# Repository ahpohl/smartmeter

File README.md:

# Overview

The project started when my mechanical [Ferraris energy counter](https://en.wikipedia.org/wiki/Electricity_meter) was replaced with a digital [smart meter](resources/ebz/datenblatt_dd3.pdf) from eBZ. The DD3 model provides an IR signal which can be read once a second with a simple IR receiver. Initially I used just an Arduino with a [photo transistor circuit](https://github.com/ahpohl/smartmeter/wiki/Arduino-breadboard) on a breadboard to read the signal. Later I have built an [IR dongle](https://github.com/ahpohl/smartmeter/wiki/IR-dongle-pcb) on a real PCB in a nice case for permanent mounting on top of the smart meter.

For the software side, the Smartmeter program reads the raw stream of data from the energy meter and forwards it as a JSON formatted string to a MQTT broker on the network. The data is stored in a TimescaleDB database and visualised on a Grafana dashboard. The installation of the software stack including the setup and maintainance of the database is described on separate [wiki pages](https://github.com/ahpohl/smartmeter/wiki).

## Build instructions

If you need to compile Smartmeter directly from source, a Makefile for (cross-)compilation is provided:

```
make CROSS_COMPILE=aarch64-unknown-linux-gnu
make install
```

Alternatively, there is also an Arch Linux package of [Smartmeter](https://aur.archlinux.org/packages/smartmeter) published in the AUR. 

## Installation

The Arch Linux package provides a systemd service file and installs the configuration file in `/etc/smartmeter/smartmeter.conf`. The service can be started with:

```
systemctl start smartmeter
```

When building directly from source, the daemon can be directly started with:

```
smartmeter --config resources/config/smartmeter_example.conf

```

## Run in Docker

The Arch Linux package installs a docker compose in `/etc/smartmeter/docker-compose.yaml` and a `Dockerfile`. Alternatively, these files are also in the root folder or the source. Before building and starting the container, the serial device used by the IR dongle needs to be set in `docker-compose.yaml` in addtion to `smartmeter.conf` to give Docker access to the IR dongle device.

```
docker-compose up --build
```

## Configuration

The Smartmeter program is configured with a configuration file located in `/etc/smartmeter/smartmeter.conf`. At least the serial device of the IR dongle, the MQTT hostname and topic to publish to needs to be set. Optionally, Smartmeter supports MQTT password authentication and TLS connection encryption. Finally, the electricity tariff, which usually consistsa price per kWh and a monthly (yearly) charge, needs to be set here for the current bill to be shown on the dashboard.

A minimal `smartmeter.conf` config file looks like this:

```
serial_device /dev/ttyUSB0
mqtt_topic smartmeter
mqtt_broker localhost
basic_rate 175.91
price_kwh 0.1983
```

## Smartmeter output

There are two versions of the EBz smart meter, the OD-types and the SM-types. According to the [manual](resources/ebz/ebz_manual.pdf), the OD-type uses the following communication parameters: 9600 Baud, 7 data bits, even parity and 1 stop bit. The serial data can be read directly with a terminal program such as picocom:

```
picocom -b 9600 -d 7 -y e /dev/ttyUSB0

/EBZ5DD3BZ06ETA_107                # '/' start marker, serial number

1-0:0.0.0*255(1EBZ0100507409)      # custom ID
1-0:96.1.0*255(1EBZ0100507409)     # device ID
1-0:1.8.0*255(000125.25688570*kWh) # energy meter
1-0:16.7.0*255(000259.20*W)        # total power
1-0:36.7.0*255(000075.18*W)        # L1 phase power
1-0:56.7.0*255(000092.34*W)        # L2 phase power
1-0:76.7.0*255(000091.68*W)        # L3 phase power
1-0:32.7.0*255(232.4*V)            # L1 phase voltage
1-0:52.7.0*255(231.7*V)            # L2 phase voltage
1-0:72.7.0*255(233.7*V)            # L3 phase voltage
1-0:96.5.0*255(001C0104)           # status
0-0:96.8.0*255(00104443)           # sensor lifetime in secs, 0x
!                                  # '!' end marker
```

Example JSON published by Smartmeter in the `smartmeter/live` topic:

```
[{
  "lifetime":150705410,     # sensor lifetime in secs, 0x
  "energy":17894.01494491,  # AC energy, kWh
  "power":228.46,           # AC power, W
  "power_l1":47.5,          # AC L1 phase power, W 
  "power_l2":66.68,         # AC L2 phase power, W
  "power_l3":114.28,        # AC L3 phase power, W
  "voltage_l1":233.1,       # Voltage L1 phase, V
  "voltage_l2":231.4,       # Voltage L2 phase, V
  "voltage_l3":233,         # Voltage L3 phase, V
  "status":"001C0104",      # EBz status
  "rate":246.13,            # price plan serice charge, € (or whatever)
  "price":0.2445,           # cost per kWh
  "time":1729973193908      # timestamp, secs since epoch
},
{
  "serial":"EBZ5DD3BZ06ETA_107",
  "custom_id":"1EBZ0100507409",
  "device_id":"1EBZ0100507409"
}]
```

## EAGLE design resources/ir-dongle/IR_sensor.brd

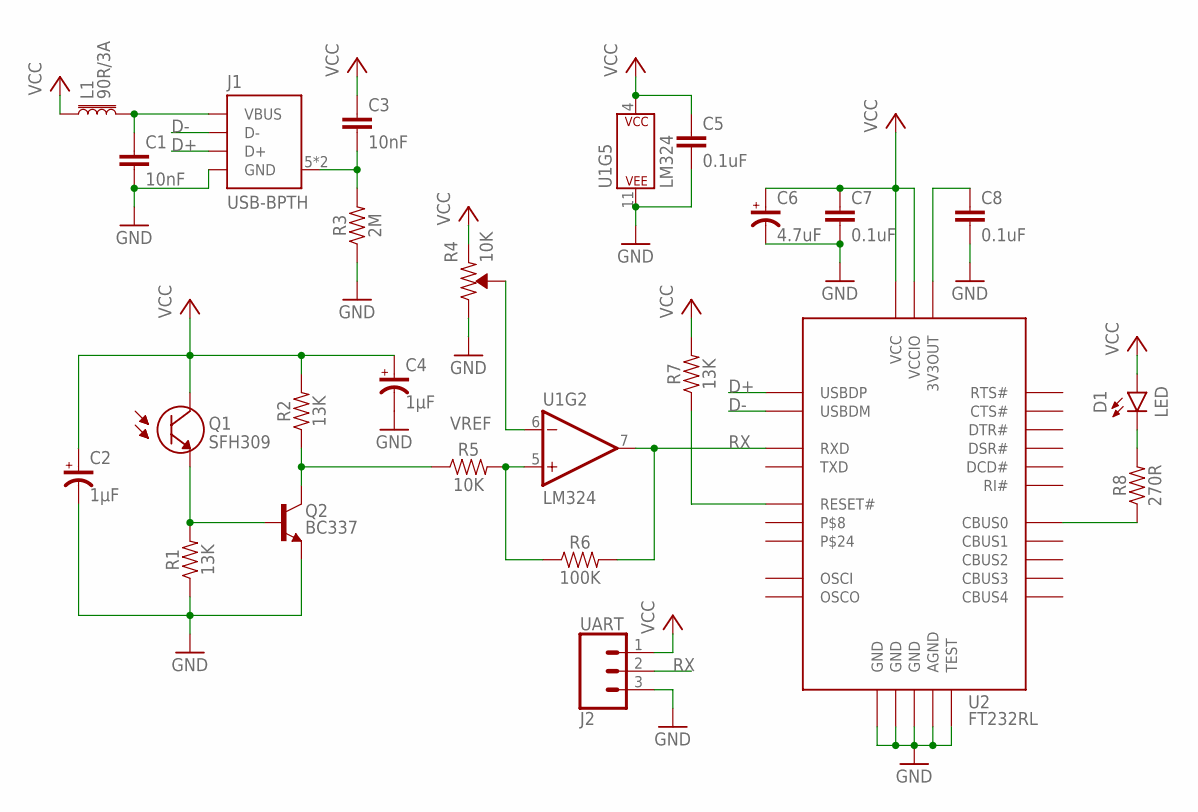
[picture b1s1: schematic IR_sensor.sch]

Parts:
C1: 10nF; CAP-PTH-2.5MM
C2, C4: 1µF; CPOL-RADIAL-2.5MM-5MM
C3: 10nF; CAP-PTH-5MM
C5, C7, C8: 0.1uF; CAP-PTH-5MM
C6: 4.7uF; CPOL-RADIAL-2.5MM-5MM
D1: LED; LED_5MM
J1: USB-BPTH; USB-B-PTH
J2: UART; 1X03
L1: 90R/3A; AXIAL-0.3
Q1: SFH309; LED_3MM_R
Q2: BC337; TO-92
R1, R2, R7: 13K; AXIAL-0.3
R3: 2M; AXIAL-0.3
R4: 10K; TRIMPOT
R5: 10K; AXIAL-0.3
R6: 100K; AXIAL-0.3
R8: 270R; AXIAL-0.3
U1: LM324; DIP14
U2: FT232RL; TSSOP-28-BL

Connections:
ADC: Q2.3 (C), R2.P$1 (1), R5.P$1 (1)
D+: J1.3 (D+), U2.15 (USBDP)
D-: J1.2 (D-), U2.16 (USBDM)
GND: C1.2, C2.2 (-), C4.2 (-), C5.2, C6.2 (-), C7.2, C8.2, J1.4 (GND), J2.3, Q2.1 (E), R1.P$1 (1), R3.P$1 (1), R4.P$2 (CW), U1.11 (P$V-), U2.7 (GND), U2.18 (GND), U2.21 (GND), U2.25 (AGND), U2.26 (TEST)
unnamed: C1.1, J1.1 (VBUS), L1.P$2 (2)
unnamed: R5.P$2 (2), R6.P$1 (1), U1.5 (+IN)
unnamed: Q1.A (E), Q2.2 (B), R1.P$2 (2)
unnamed: C8.1, U2.17 (3V3OUT)
unnamed: D1.K, R8.P$2 (2)
unnamed: R8.P$1 (1), U2.23 (CBUS0)
unnamed: C3.2, J1.5 (SHIELD), J1.6 (SHIELD), R3.P$2 (2)
unnamed: R7.P$1 (1), U2.19 (RESET#)
RX: J2.2, R6.P$2 (2), U1.7 (OUT), U2.5 (RXD)
VCC: C2.1 (+), C3.1, C4.1 (+), C5.1, C6.1 (+), C7.1, D1.A, J2.1, L1.P$1 (1), Q1.K (C), R2.P$2 (2), R4.P$1 (CCW), R7.P$2 (2), U1.4 (P$V+), U2.4 (VCCIO), U2.20 (VCC)
VREF: R4.P$3 (WIPER), U1.6 (-IN)

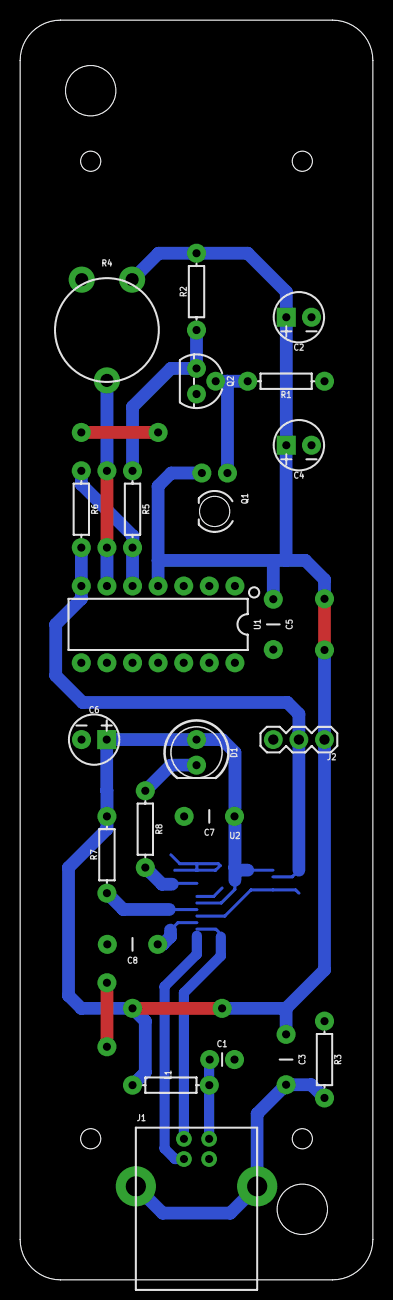
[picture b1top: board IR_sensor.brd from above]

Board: 2 copper layers, 35.0 x 125.0 mm, 24 parts (0 on the bottom side), 15 nets.

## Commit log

2020-01-29 intital commit
2020-01-29 get d0 datagram from serial port
2020-01-29 added .gitignore
2020-01-29 make serial buffer static
2020-01-29 cleanup git build dir
2020-01-29 cleanup git main.o
2020-01-30 allocate dynamic serial buffer
2020-01-30 datagram validity check
2020-01-30 parsed serial num and device id
2020-01-30 read d0 datagram complete
2020-01-31 setup write obis thread
2020-01-31 smartmeter functional version
2020-01-31 fix wrong variable initialisation
2020-01-31 fix Makefile install target
2020-01-31 fix missing backslash
2020-01-31 convert sensor time to unsigned long
2020-01-31 fix sensor time format for meterN
2020-01-31 add sensor lifetime in days
2020-02-01 remove set ramdisk function
2020-02-01 const correctness
2020-08-12 publish to MQTT broker
2020-08-12 run MQTT publish in its own thread
2020-08-12 wait before publish obis and mqtt
2020-08-13 add topic parameter
2020-08-13 send MQTT every 10 minutes
2020-08-13 commented publish power to MQTT
2020-08-13 publish MQTT power only in debug
2020-08-14 initial README.md text
2020-08-14 add mqtt to influxdb bridge files
2020-08-14 remove MQTT power function
2020-08-15 remove unneeded includes
2020-08-15 publish MQTT json string
2020-08-15 convert m_sensortime to seconds only once
2020-08-15 control precsion of obex and mqtt output
2020-08-15 updated README influxdb
2020-08-15 set obis precision of lifetime
2020-08-15 MQTT json output fields and tags
2020-08-15 put lifetime output first
2020-08-15 MQTT json output as floats
2020-08-15 updated retention policy and continuous query
2020-08-15 README.md json fields and tags string
2020-08-15 remove mqtt to influxdb bridge script
2020-08-21 add node-red flow
2020-08-21 updated README, grafana dashboard
2020-08-22 add influxdb continuous queries into README
2020-08-23 modified grafana dashboard
2020-08-23 add electricity tariff details
2020-08-23 rename tariff options
2020-08-23 fix price and rate options
2020-08-24 add meterN dashboard
2020-08-24 mqtt rate and price move to fields
2020-08-29 fix path in smartmeter.conf
2020-09-04 add grafana dashboard screenshot
2020-09-20 updated README, inserted links
2020-12-04 mosq reconnect and resend
2020-12-04 publish in do while loop
2020-12-04 wait before reconnect
2020-12-04 add reconnect_async call
2021-01-05 basic rate per month
2021-01-05 add IR dongle schematics
2021-01-05 rename schematics
2021-01-05 correct schematic name
2021-01-05 add node-red flow chart
2021-01-05 updated grafana dash json
2021-02-15 updated schematic and dashboard
2021-03-08 include unix epoch timestamp with ms precision
2021-03-08 save timestamp earlier when receiving data
2021-03-08 timestamp before reading datagram
2021-03-09 timestamp protected by mutex
2021-03-13 singled threaded, keep obis codes
2021-03-13 handle shutdown with signals
2021-03-13 update changelog
2021-03-13 grafana flux queries
2021-03-13 rename flux query file
2021-03-13 update grafana flux queries
2021-03-13 add influxdb tasks
2021-03-13 daily task group results by field
2021-03-14 update daily task flux
2021-03-14 update daily task
2021-03-14 update and optimise daily task
2021-03-23 move status into json value array
2021-03-23 remove second time value
2021-03-23 move status up
2021-04-01 move from influxdb to timescaledb
2021-04-01 remove influxdb files
2021-04-02 clean up
2021-04-06 Delete IR-dongle_schematic.png
    MCP2221 does not support 7 bit data mode and hence does not work for the OD version of the smartmeter
2021-04-17 grafana dashboard timeseries plots
2021-04-17 add schematic with FT232RL
2021-04-19 add pcb process
2021-05-09 enable even parity checking
2021-05-09 add eagle files
2021-05-09 remove EOM from d0.log
2021-05-09 use shared pointer in main
2021-05-23 release publish online/offline status
2021-05-23 add auth to mqtt class
2021-05-23 support mqtt username and password
2021-05-23 fix type in config file
2021-05-23 change reason_code into connack_code
2021-05-25 enable TLS, no server cert checking, no client certs
2021-05-25 connection TLS enabled
2021-05-25 update readme and changelog
2021-05-26 Revert "Update README.md"
    This reverts commit c782abcb954976815a0ef9e2b79eb43e2e82a3e6.
2021-05-26 Revert "Update README.md"
    This reverts commit 4d74c51eb6688a3e69187eb757d56f544f73e49c.
2021-05-26 Revert "Update README.md"
    This reverts commit 95f2e60795c3afd906bca35778d2d0a31f4a2429.
2021-05-26 Revert "Update README.md"
    This reverts commit 7963ffcb9a89f0e7c2e197022705f80680d061c4.
2021-05-26 Revert "Update README.md"
    This reverts commit be89226843cce1d0f01fbb2af5f37c76624b0fd6.
2021-05-26 initial config parser
2021-05-26 config parser adapted
2021-05-26 rename variables
2021-05-26 read config file
2021-05-26 add config file with comments
2021-05-26 basic class setup complete
2021-05-26 convert string to type
2021-05-26 fill map with key value pairs
2021-05-26 ignore config executable
2021-05-26 parse key value pairs into map
2021-05-26 add display config function
2021-05-27 get value as inline function
2021-05-27 add const to methods
2021-05-27 make string default data type for GetValue
2021-05-27 implement get ... functions
2021-05-27 check valid_keys
2021-05-27 use config in smartmeter class
2021-05-27 edit main getopt arguments
2021-05-27 checking config arguments
2021-05-27 checked most arguments
2021-05-27 clean up includes, check config complete
2021-05-28 project cleanup
2021-05-28 enable TLS, add config file
2021-05-29 remove systemd config file
2021-05-30 updated sql scripts
2021-05-30 cagg average power
2021-05-30 updated grafana dashboard
2021-05-30 edit comments in sql scripts
2021-05-30 average power phases
2021-05-31 update grafana dashboard
2021-06-04 change cagg_power retention time
2021-06-13 publish data into /live topic
2021-06-16 rename pg_cron jobs
2021-09-26 add Dockerfile for node-red
2021-09-26 node-red credential file not working
2021-09-26 node-red credentials working
2021-09-27 docker node-red and timescaledb containers ok
2021-09-27 timescaledb container running
2021-09-28 move customizations to custom.sql
2021-10-03 Revert "add Dockerfile for node-red"
    This reverts commit c09ee220cf7a45331acffbf8682e2ff1631bd5a4.
2021-10-03 commit postgres wal archive scripts
2021-10-08 edit views.sql to include start date of archive
2022-01-02 set debug level in config file
2022-01-02 update node-red and grafana json
2022-01-07 node-red flow use smartmeter/live topic
2022-01-08 use timescaledb_experimental.time_bucket_ng()
2022-01-08 change pg_cron schedule
2022-02-02 remove indices on aggregate tables
2022-02-02 add unique constaint on archive bucket_1d
2022-02-02 insert comment in views.sql
2022-02-03 add unique indices for mat view refresh concurrently
2022-02-21 log buffer before sync check
2022-02-21 do not exit on serial receive error
2022-04-06 add averages to montly view
2022-10-30 update smartmeter.conf example
2022-12-29 update smartmeter mqtt class
2022-12-29 fix status online disappears after reconnect
2022-12-29 bump changelog to new version
2022-12-29 fix typo in online message
2022-12-29 add mqtt online notify flag
2023-02-14 updated retention policies
2023-04-12 remove experimental time_bucket
2023-04-15 time buckets at local time zone
2023-04-15 update monthly plot grafana dashboard
2023-07-22 plpgsql function to calc percentages
2023-08-18 add eclipse project and cross compile option
2023-08-18 remove log enum from serial and mqtt classes
2023-08-18 silence error messages after 5
2023-08-19 flush serial buffers after out of sync
2023-08-29 show sunrise and sunset in dashboard
2023-11-07 reduce aggregate interval and grant select
2024-02-13 fix day error in trend calc
2024-02-18 add 15 min aggregate (load profile)
2024-03-07 add timeout for serial message
2024-03-26 add trend based on model
2024-03-26 update dashboard and flow
2024-03-26 get zero bytes from serial
2024-03-27 remove getbyte function
2024-03-27 reduce serial buffer size to 64
2024-03-27 log bytes_received
2024-04-04 re-init serial object upon read error
2024-04-07 read zero bytes: test serial close/reopen
2024-10-19 code formatting cleanup
2024-10-20 apply clang-format llvm
2024-10-26 add support for docker-compose and more
2024-10-27 make mqtt_port optional
2024-10-27 fix dockerfile
2024-10-27 upload new release
2024-10-27 fix broken links
2024-11-10 fix mqtt port config error
